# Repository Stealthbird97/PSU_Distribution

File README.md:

# PSU_Distribution
An interface/distribution board for HP DSP-600 server powersupplies, enabling usage as a bench PSU.
Features of this board include voltage adjustment (Increase and decrease), fused anderson powerpole connectors, adjustable fan control and daisychaining support.

Distribution section of design incorporates https://github.com/Tyler-Ward/Powerpole-distribution-board.

## Construction notes

* PCB should be made on a 2oz copper board.

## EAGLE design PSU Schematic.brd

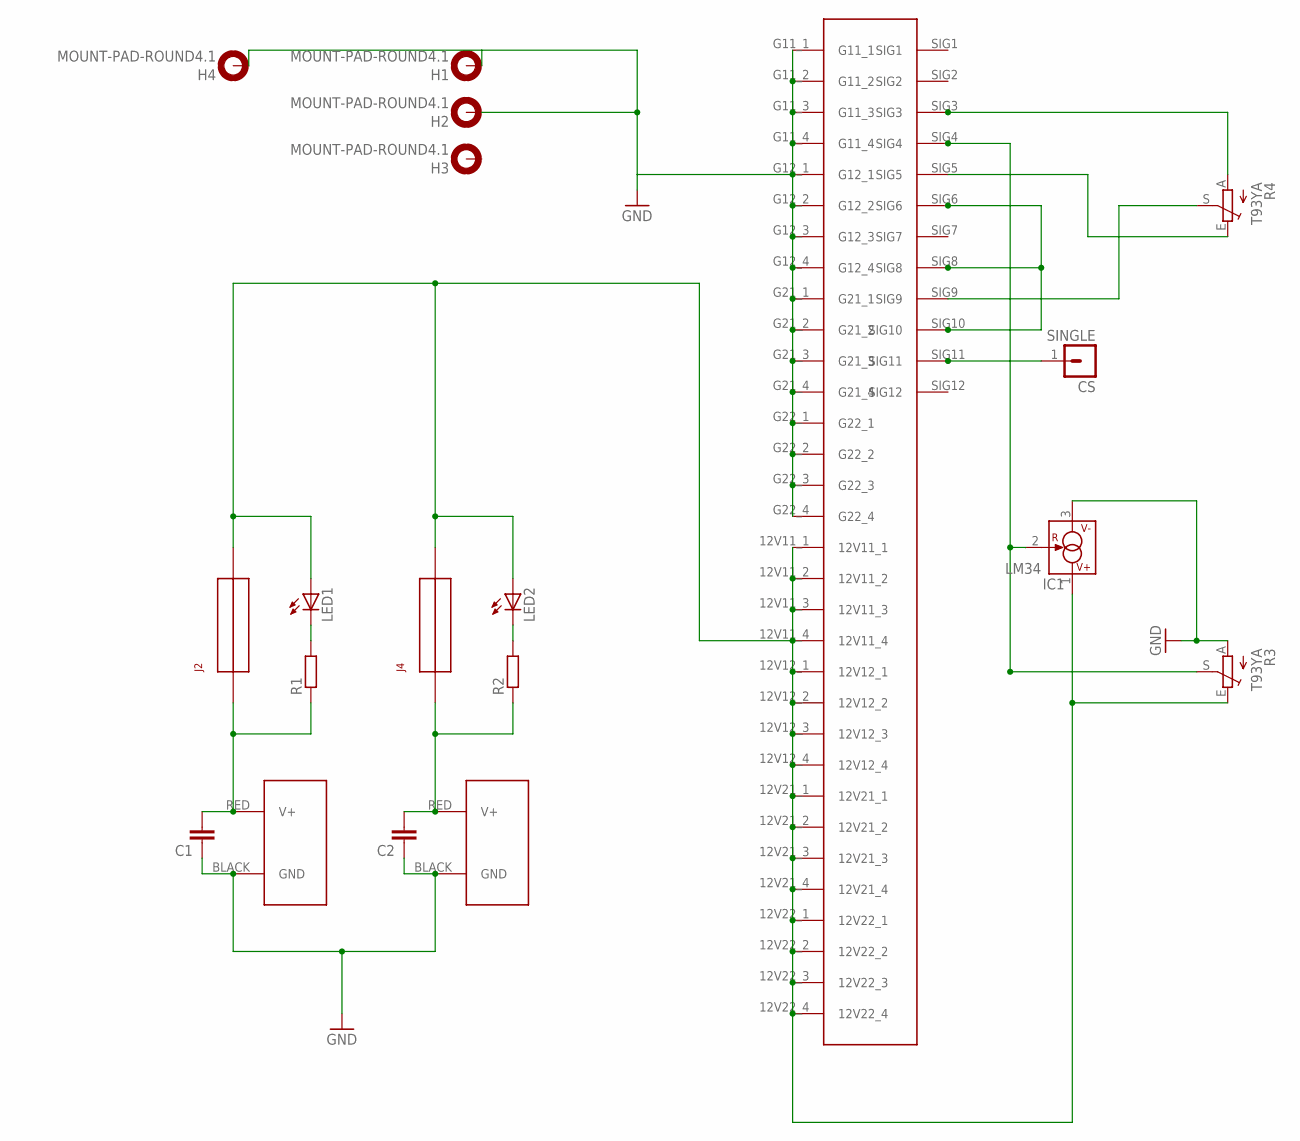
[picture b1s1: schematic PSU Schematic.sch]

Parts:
C1, C2: C-EU050-025X075; C050-025X075
CS: SINGLE
H1, H2, H3, H4: MOUNT-PAD-ROUND4.1; 4,1-PAD
IC1: LM34; TO92
J1, J3: POWERPOLE_POWER45A; POWERPOLE_PAIR_45A
J2, J4: FUSEATC; FUSE_ATC
LED1, LED2: LED3MM
R1, R2: R-EU_0204/7; 0204/7
R3, R4: T93YA; RJ9W
U$2: 51760-10201202AALF51760-10201202AALF; 51730-073LF

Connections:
5VCC: R4.A, U$2.SIG3
CURRENTSHARE: CS.1, U$2.SIG11
FAN: IC1.2 (R), R3.S, U$2.SIG4
GND: C1.1, C2.1, H1.B4,1, H2.B4,1, H4.B4,1, IC1.3 (V-), J1.BLACK (GND), J3.BLACK (GND), R3.A, U$2.G11_1, U$2.G11_2, U$2.G11_3, U$2.G11_4, U$2.G12_1, U$2.G12_2, U$2.G12_3, U$2.G12_4, U$2.G21_1, U$2.G21_2, U$2.G21_3, U$2.G21_4, U$2.G22_1, U$2.G22_2, U$2.G22_3, U$2.G22_4
LVCC: IC1.1 (V+), J2.P$3, J2.P$4, J4.P$3, J4.P$4, LED1.A, LED2.A, R3.E, U$2.12V11_1, U$2.12V11_2, U$2.12V11_3, U$2.12V11_4, U$2.12V12_1, U$2.12V12_2, U$2.12V12_3, U$2.12V12_4, U$2.12V21_1, U$2.12V21_2, U$2.12V21_3, U$2.12V21_4, U$2.12V22_1, U$2.12V22_2, U$2.12V22_3, U$2.12V22_4
unnamed: R4.E, U$2.SIG5
unnamed: R4.S, U$2.SIG9
unnamed: LED1.K (C), R1.2
unnamed: LED2.K (C), R2.2
PPV1: C1.2, J1.RED (V+), J2.P$1, J2.P$2, R1.1
PPV2: C2.2, J3.RED (V+), J4.P$1, J4.P$2, R2.1
PSON: U$2.SIG6, U$2.SIG8, U$2.SIG10

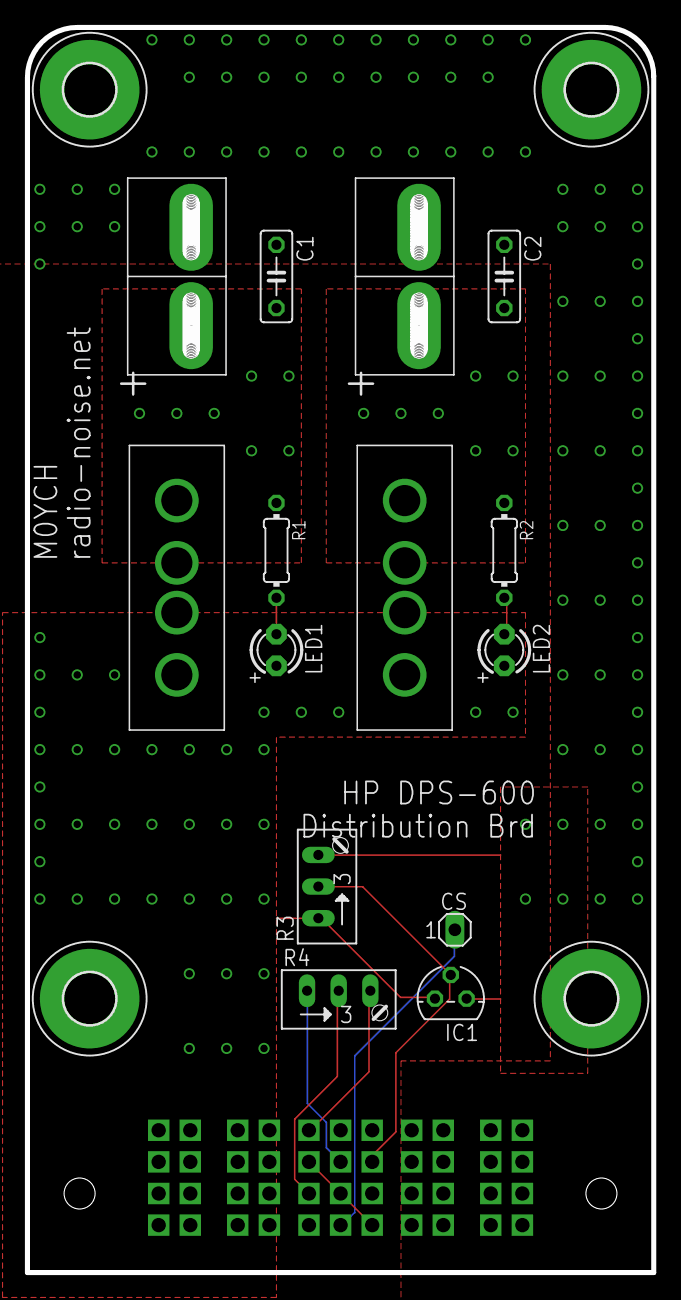
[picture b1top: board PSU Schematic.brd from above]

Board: 2 copper layers, 50.3 x 100.0 mm, 19 parts (0 on the bottom side), 12 nets.

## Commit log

2017-03-21 Initial Designs
2017-03-21 added gitignore
2017-03-21 Initial Gerbers
2017-03-21 Revert "Initial Gerbers"
    This reverts commit 7142ff8bf6605580f1301563203eff30711a4057.
2017-03-21 update project description
2017-03-22 Add gerber's to ignore
2017-03-22 Layout revision
2017-03-31 Corrected layout
    Flipped design to correct mis-match which would have occured.
2017-03-31 bStop Added
2017-03-31 Screen Details
2017-03-31 Moar Vias
2017-04-01 Connector Pin adjustment. More vias
2017-04-01 Added voltage decrease. Design Rules Updated.
